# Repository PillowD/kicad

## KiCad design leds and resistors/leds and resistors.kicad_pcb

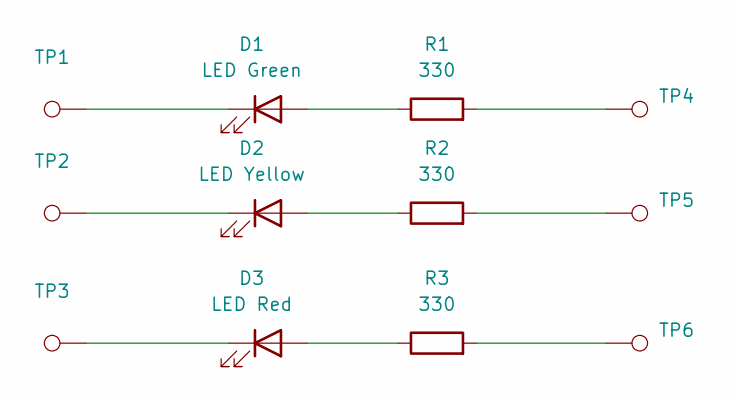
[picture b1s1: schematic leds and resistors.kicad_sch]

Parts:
D1: LED Green; LED_0805_2012Metric; MFG PN LTST-C171GKT
D2: LED Yellow; LED_0805_2012Metric; MFG PN LTST-C170KSKT
D3: LED Red; LED_0805_2012Metric; MFG PN LTST-C171KRKT
R1, R2, R3: 330; R_0805_2012Metric; MFG PN ERJ-6GEYJ331V
TP1, TP2, TP3, TP4, TP5, TP6: TestPoint_Pad_D2.0mm

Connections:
unnamed: D1.2 (A), R1.1
unnamed: D1.1 (K), TP1.1
unnamed: D2.2 (A), R2.1
unnamed: D2.1 (K), TP2.1
unnamed: D3.2 (A), R3.1
unnamed: D3.1 (K), TP3.1
unnamed: R1.2, TP4.1
unnamed: R2.2, TP5.1
unnamed: R3.2, TP6.1

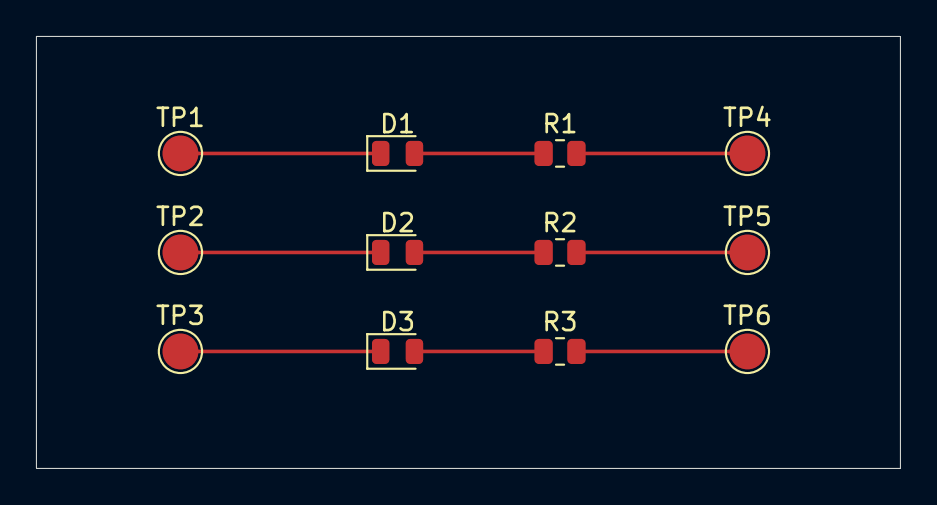
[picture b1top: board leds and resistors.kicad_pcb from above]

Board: 2 copper layers, 48.0 x 24.0 mm, 12 parts (0 on the bottom side), 9 nets.

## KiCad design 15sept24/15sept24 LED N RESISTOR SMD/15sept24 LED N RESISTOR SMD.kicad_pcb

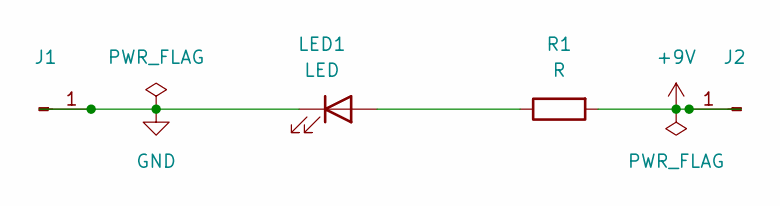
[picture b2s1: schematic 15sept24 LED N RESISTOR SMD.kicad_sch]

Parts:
J1, J2: Conn_01x01_Pin; PinHeader_1x01_P1.00mm_Vertical
LED1: LED; LED_0603_1608Metric
R1: R; R_0603_1608Metric

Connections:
+9V: J2.1, R1.2
GND: J1.1, LED1.1 (K)
unnamed: LED1.2 (A), R1.1

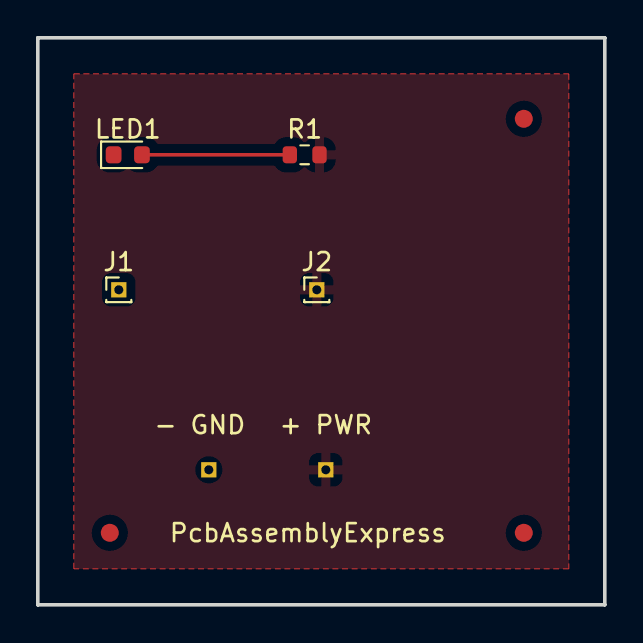
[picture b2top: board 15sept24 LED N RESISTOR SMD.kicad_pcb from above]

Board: 2 copper layers, 31.5 x 31.5 mm, 7 parts (0 on the bottom side), 3 nets.

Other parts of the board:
FIdLL: Fiducial_1mm_Mask2mm
FidLR: Fiducial_1mm_Mask2mm
FidUR: Fiducial_1mm_Mask2mm

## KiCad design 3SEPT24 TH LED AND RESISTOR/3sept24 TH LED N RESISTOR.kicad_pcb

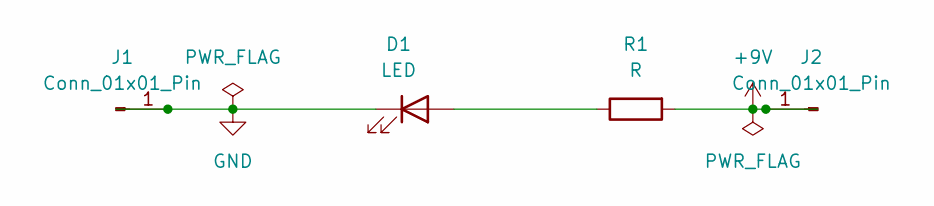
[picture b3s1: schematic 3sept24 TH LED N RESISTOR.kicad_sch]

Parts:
D1: LED; LED_D3.0mm
J1, J2: Conn_01x01_Pin; PinHeader_1x01_P1.00mm_Vertical
R1: R; R_Axial_DIN0204_L3.6mm_D1.6mm_P7.62mm_Horizontal

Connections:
+9V: J2.1, R1.2
GND: D1.1 (K), J1.1
unnamed: D1.2 (A), R1.1

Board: 2 copper layers, 4 parts (0 on the bottom side), 3 nets, no tracks yet.

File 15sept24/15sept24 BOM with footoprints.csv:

Item Number,Ref Des,Quantity,MFG PN,Vendor PN,Description,Side,Part Type,Package,DNP DNS,Datasheet
1,LED1,1,QBLP601-R,1516-1059-1-ND,LED RED CLEAR 0603 SMD,Top,SMT,603,,https://www.qt-brightek.com/datasheet/QBLP601_series.pdf
2,R1,1,RC0603FR-071KL,311-1.00KHRCT-ND,RES 1K OHM 1% 1/10W 0603,Top,SMT,603,,https://www.yageo.com/upload/media/product/products/datashee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
3,J1,0,PH1-01-UA,2057-PH1-01-UA-ND,CONN HEADER VERT 1POS 2.54MM,Top,TH,TH,DNP,https://app.adam-tech.com/products/download/data_sheet/20160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
4,J1,0,PH1-01-UA,2057-PH1-01-UA-ND,CONN HEADER VERT 1POS 2.54MM,Top,TH,TH,DNP,https://app.adam-tech.com/products/download/data_sheet/20160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
